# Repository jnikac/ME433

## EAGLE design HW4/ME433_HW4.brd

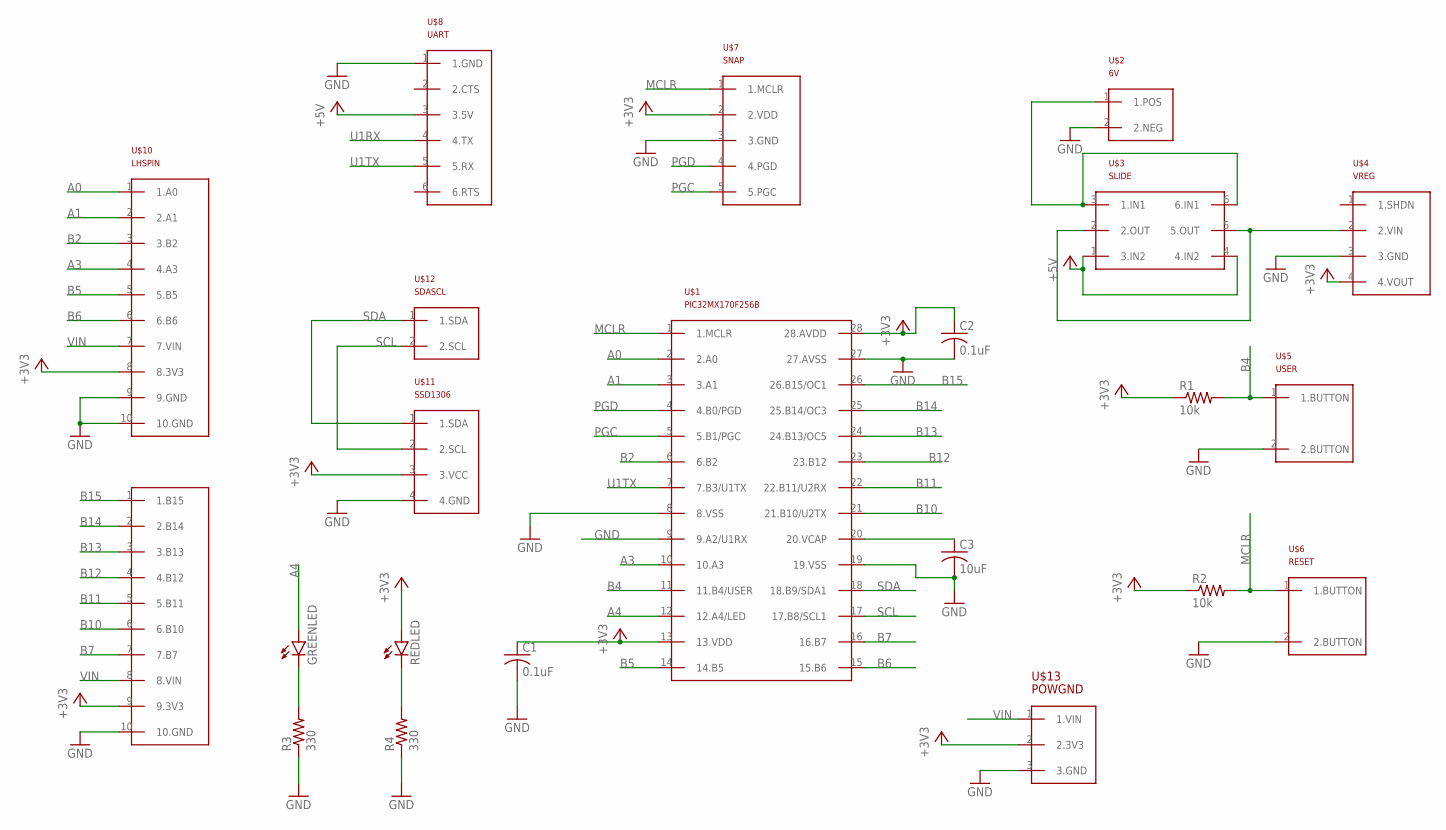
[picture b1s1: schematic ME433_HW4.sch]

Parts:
C1, C2: 0.1uF; C025-030X050
C3: 10uF; C025-030X050
GREENLED: LED3MM
R1, R2: 10k; 0207/10
R3, R4: 330; 0207/10
REDLED: LED3MM
U$1: PIC32MX170F256B; DIL28-3
U$2: 6V
U$3: SLIDE; 2X3
U$4: VREG
U$5: USER; BUTTON
U$6: RESET; BUTTON
U$7: SNAP; 1X05
U$8: UART
U$9: RHS_PIN; RHSPIN
U$10: LHSPIN
U$11: SSD1306
U$12: SDASCL
U$13: POWGND

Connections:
+3V3: C1.1, C2.1, R1.1, R2.1, REDLED.A, U$1.13 (13.VDD), U$1.28 (28.AVDD), U$4.4 (4.VOUT), U$7.2 (2.VDD), U$9.9 (9.3V3), U$10.8 (8.3V3), U$11.3 (3.VCC), U$13.2 (2.3V3)
+5V: U$3.1 (3.IN2), U$3.4 (4.IN2), U$8.3 (3.5V)
A0: U$1.2 (2.A0), U$10.1 (1.A0)
A1: U$1.3 (3.A1), U$10.2 (2.A1)
A3: U$1.10 (10.A3), U$10.4 (4.A3)
A4: GREENLED.A, U$1.12 (12.A4/LED)
B2: U$1.6 (6.B2), U$10.3 (3.B2)
B4: R1.2, U$1.11 (11.B4/USER), U$5.1 (1.BUTTON)
B5: U$1.14 (14.B5), U$10.5 (5.B5)
B6: U$1.15 (15.B6), U$10.6 (6.B6)
B7: U$1.16 (16.B7), U$9.7 (7.B7)
B10: U$1.21 (21.B10/U2TX), U$9.6 (6.B10)
B11: U$1.22 (22.B11/U2RX), U$9.5 (5.B11)
B12: U$1.23 (23.B12), U$9.4 (4.B12)
B13: U$1.24 (24.B13/OC5), U$9.3 (3.B13)
B14: U$1.25 (25.B14/OC3), U$9.2 (2.B14)
B15: U$1.26 (26.B15/OC1), U$9.1 (1.B15)
GND: C1.2, C2.2, C3.2, R3.1, R4.1, U$1.8 (8.VSS), U$1.19 (19.VSS), U$1.27 (27.AVSS), U$2.2 (2.NEG), U$4.3 (3.GND), U$5.2 (2.BUTTON), U$6.2 (2.BUTTON), U$7.3 (3.GND), U$8.1 (1.GND), U$9.10 (10.GND), U$10.9 (9.GND), U$10.10 (10.GND), U$11.4 (4.GND), U$13.3 (3.GND)
MCLR: R2.2, U$1.1 (1.MCLR), U$6.1 (1.BUTTON), U$7.1 (1.MCLR)
unnamed: U$2.1 (1.POS), U$3.3 (1.IN1), U$3.6 (6.IN1)
unnamed: R4.2, REDLED.K (C)
unnamed: GREENLED.K (C), R3.2
unnamed: C3.1, U$1.20 (20.VCAP)
PGC: U$1.5 (5.B1/PGC), U$7.5 (5.PGC)
PGD: U$1.4 (4.B0/PGD), U$7.4 (4.PGD)
SCL: U$1.17 (17.B8/SCL1), U$11.2 (2.SCL), U$12.2 (2.SCL)
SDA: U$1.18 (18.B9/SDA1), U$11.1 (1.SDA), U$12.1 (1.SDA)
U1RX: U$1.9 (9.A2/U1RX), U$8.4 (4.TX)
U1TX: U$1.7 (7.B3/U1TX), U$8.5 (5.RX)
VIN: U$3.2 (2.OUT), U$3.5 (5.OUT), U$4.2 (2.VIN), U$9.8 (8.VIN), U$10.7 (7.VIN), U$13.1 (1.VIN)

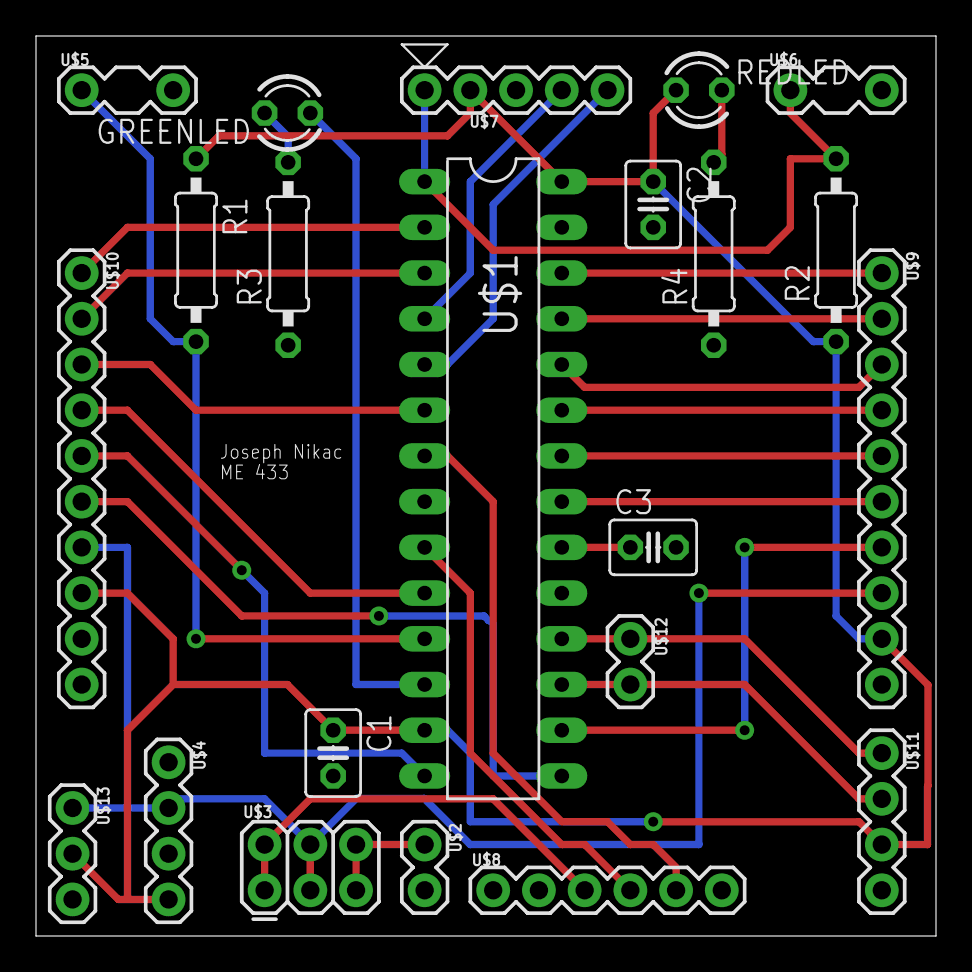
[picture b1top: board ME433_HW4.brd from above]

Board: 2 copper layers, 50.0 x 50.0 mm, 22 parts (0 on the bottom side), 30 nets.

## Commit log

2022-05-23 hws
    hws
2022-06-09 HW11
